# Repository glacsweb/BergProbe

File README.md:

# BergProbe
Repository for schematics and PCB layouts for the 2017 BergProbes.

### BergProbe/
Contains layouts for the BergProbe schematic (control+power board)

### BergProbe-Adapter/
Contains layouts for a breakout board for GPS and Radio modules, with connector for connecting to BergProbe board.

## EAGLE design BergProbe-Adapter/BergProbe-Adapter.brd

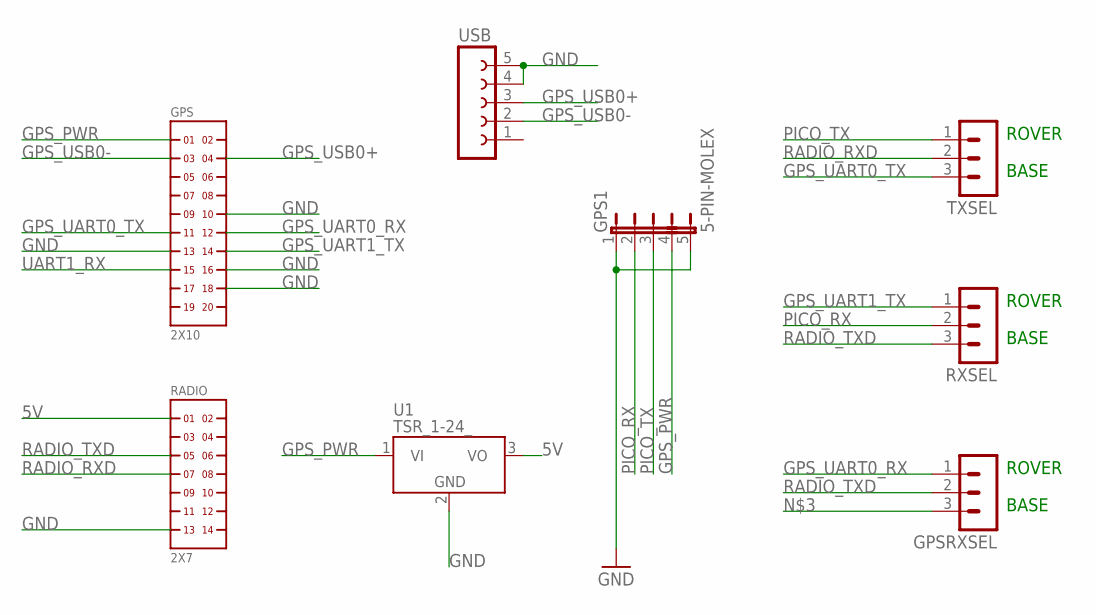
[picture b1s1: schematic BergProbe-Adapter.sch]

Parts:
GPS: 2X10
GPS1: 5-PIN-MOLEX; 5-MOLEX
GPSRXSEL: MA03-1
RADIO: 2X7
RXSEL: MA03-1
TXSEL: MA03-1
U1: TSR_1-24_; TSR-1
USB: FE05-1

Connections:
5V: RADIO.1, U1.3 (VO)
GND: GPS.10, GPS.13, GPS.16, GPS.18, GPS1.1, GPS1.5 (6), RADIO.13, U1.2 (GND), USB.4, USB.5
GPS_PWR: GPS.1, GPS1.4, U1.1 (VI)
GPS_UART0_RX: GPS.12, GPSRXSEL.1
GPS_UART0_TX: GPS.11, TXSEL.3
GPS_UART1_TX: GPS.14, RXSEL.1
GPS_USB0+: GPS.4, USB.3
GPS_USB0-: GPS.3, USB.2
PICO_RX: GPS1.2, RXSEL.2
PICO_TX: GPS1.3, TXSEL.1
RADIO_RXD: RADIO.7, TXSEL.2
RADIO_TXD: GPSRXSEL.2, RADIO.5, RXSEL.3
UART1_RX: GPS.15

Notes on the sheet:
ROVER
BASE

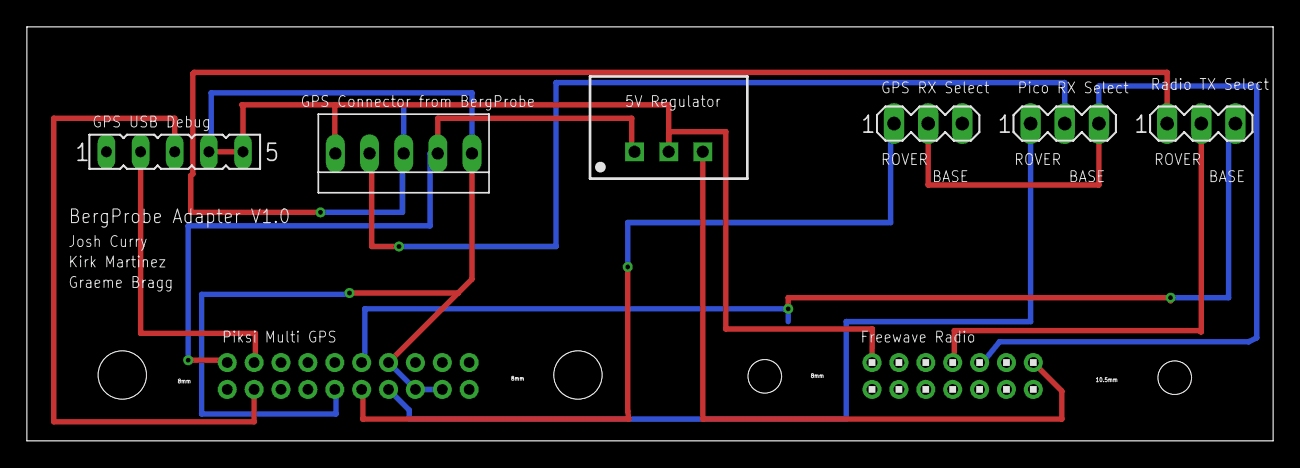
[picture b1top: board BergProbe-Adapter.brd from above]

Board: 2 copper layers, 92.7 x 30.8 mm, 8 parts (1 on the bottom side), 12 nets.

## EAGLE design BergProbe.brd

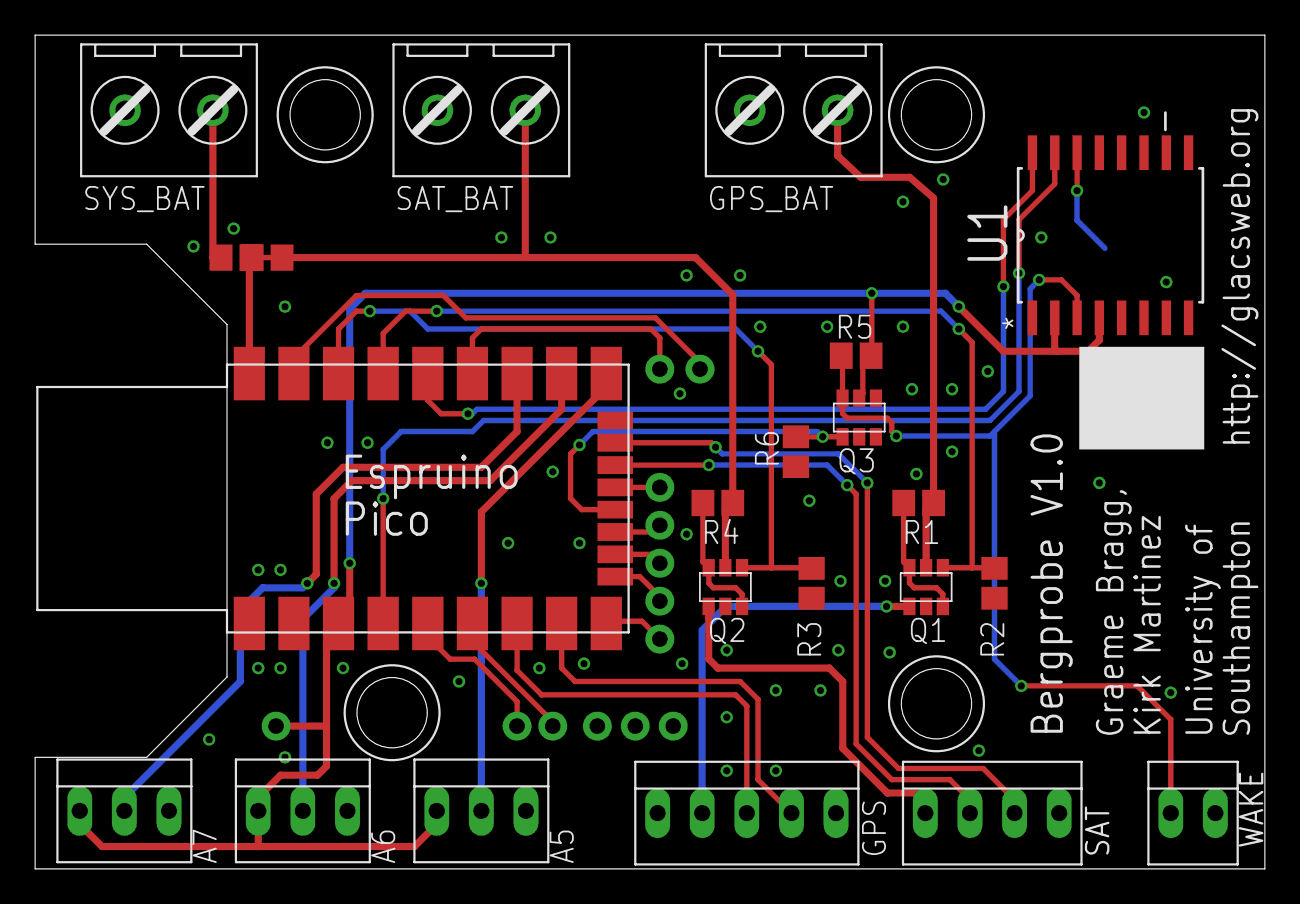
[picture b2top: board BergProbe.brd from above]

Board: 2 copper layers, 70.0 x 47.5 mm, 23 parts (1 on the bottom side), 23 nets.

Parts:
A5, A6, A7: 3-PIN-MOLEX; 3-MOLEX
GPS: 5-PIN-MOLEX; 5-MOLEX
GPS_BAT: HEADER_2; LUMBERG_CAGE_2
Q1, Q2, Q3: DMG6602SVT; TSOT26
R1, R2, R3, R4, R5, R6: 100K; R0805
R500, R600: DNP; R0805
SAT: 4-PIN-MOLEX; 4-MOLEX
SAT_BAT: HEADER_2; LUMBERG_CAGE_2
SYS_BAT: HEADER_2; LUMBERG_CAGE_2
U1: DS3231SN; SOIC127P1032X265-16N
U$1: ESPRUINO_PICO_SMDONLY
U$2: BUTTON_CELL_NEW; CR2016
WAKE: 2-PIN-MOLEX; 2-MOLEX

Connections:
+3V3: A5.3, A6.3, A7.3, Q3.P$2, R5.2, U1.2, U1.4, U$1.3.3V
ADC_A5: A5.2, U$1.A5
ADC_A6: A6.2, U$1.A6
ADC_A7: A7.2, U$1.A7
GND: A5.1, A6.1, A7.1, GPS.1, GPS.5, GPS_BAT.1, Q1.P$5, Q2.P$5, Q3.P$1, Q3.P$5, Q3.P$6, R2.1, R3.1, R6.1, SAT.1, SAT_BAT.1, SYS_BAT.1, U1.5, U1.6, U1.7, U1.8, U1.9, U1.10, U1.11, U1.12, U1.13, U$1.GND, U$2.GND, WAKE.1
GPS_BAT: GPS_BAT.2, Q1.P$2, R1.2
GPS_EN: Q1.P$1, R2.2, U$1.B13
GPS_PWR: GPS.4, Q1.P$4
I2C_SCK: U1.16, U$1.B10
I2C_SDA: U1.15, U$1.B3
unnamed: Q1.P$3, Q1.P$6, R1.1
unnamed: Q2.P$3, Q2.P$6, R4.1
RTC_BAT: U1.14, U$2.V+@2
RTC_INT: Q3.P$3, R5.1, U1.3, WAKE.2
SAT_BAT: Q2.P$2, R4.2, R500.1, R500.2, R600.2, SAT_BAT.2, U$1.BAT
SAT_EN: Q2.P$1, R3.2, U$1.B14
SAT_PWR: Q2.P$4, SAT.4
SYS_BAT: R600.1, SYS_BAT.2
USART1_RX: GPS.2, U$1.B7
USART1_TX: GPS.3, U$1.B6
USART2_RX: SAT.2, U$1.A3
USART2_TX: SAT.3, U$1.A2
WAKE: Q3.P$4, R6.2, U$1.A0

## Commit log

2017-06-14 Initial commit with base schematic
2017-06-14 Initial (incomplete) PCB Layout.
2017-06-17 Progress on PCB layout. Added analogue headers to schematic.
2017-06-18 PCB Layout complete EXCEPT for wakeup switch/RTC Alarm finalisation.
2017-06-22 FInal PCB and schematic version
2017-06-22 brd tweak
2017-06-22 Gerber files added
2017-07-20 Moved files into directory structure
2017-07-20 Added BergProbe-Adapter Schematic and PCB for review.
2017-07-20 Corrected Readme syntax
2017-07-20 Added mounting holes. Will need checking; only done roughly with callipers.
2017-07-20 Modified hole placings. Also moved tracks away from holes just in case.
2017-07-20 Changed text layer so not on copper.
2017-07-21 Oops removed small track stubs
2021-05-27 first upload of Ublox M9 based glacier tracker
2021-05-27 a bit more explanation
